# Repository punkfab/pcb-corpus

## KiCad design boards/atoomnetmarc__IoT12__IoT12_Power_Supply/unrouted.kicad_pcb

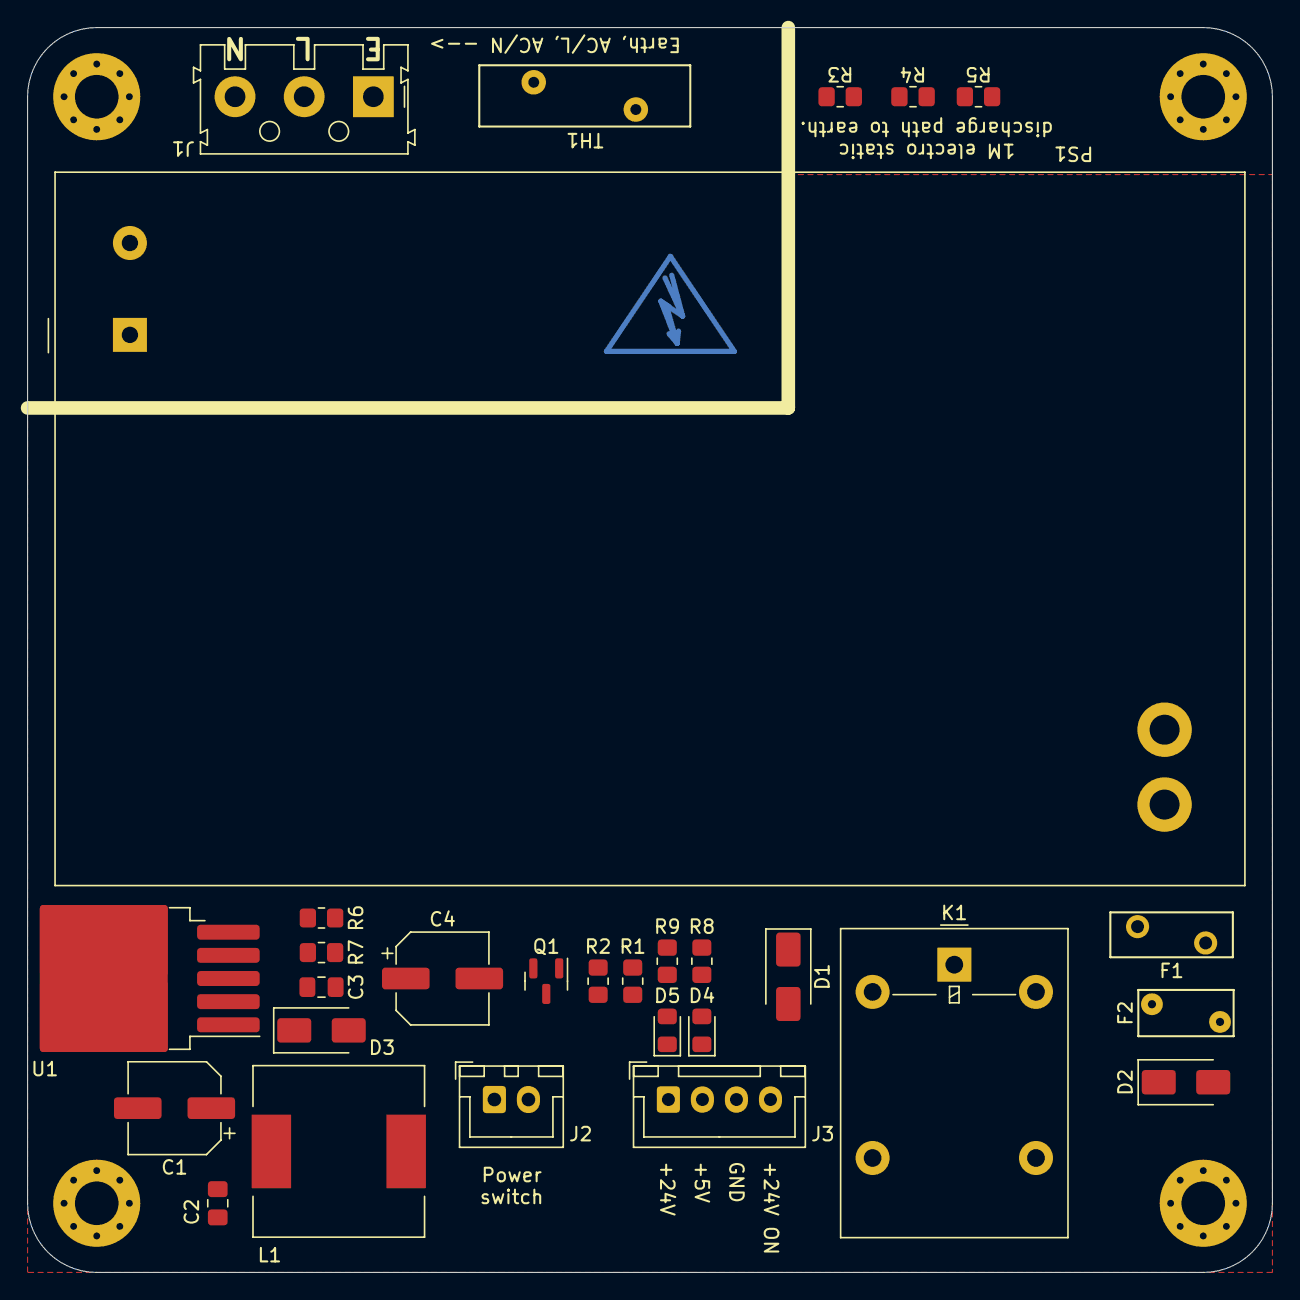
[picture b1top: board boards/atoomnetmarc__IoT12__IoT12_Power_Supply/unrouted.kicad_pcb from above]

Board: 2 copper layers, 91.4 x 91.4 mm, 33 parts (0 on the bottom side), 21 nets, no tracks yet.

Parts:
C1, C4: 100uF/35V; CP_Elec_6.3x7.7
C2, C3: 100nF; C_0805_2012Metric_Pad1.18x1.45mm_HandSolder
D1: SS14; D_SMA
D2, D3: SS34; D_SMA
D4, D5: Blue; LED_0805_2012Metric_Pad1.15x1.40mm_HandSolder
F1: PTC 1.5A/30V; RV_Disc_D9mm_W3.3mm_P5mm
F2: PTC 0.5A/30V; RV_Disc_D7mm_W3.4mm_P5mm
H1, H2, H3, H4: MountingHole; MountingHole_3.2mm_M3_Pad_Via
J1: Screw_Terminal_01x03; TerminalBlock_Weidmueller-PM-5.08-03-90-3.5SN-BK-BX
J2: JST B2B-XH-A; JST_XH_B2B-XH-A_1x02_P2.50mm_Vertical
J3: JST B4B-XH-A; JST_XH_B4B-XH-A_1x04_P2.50mm_Vertical
K1: Omron G5LE-1 24VDC; Relay_SPDT_Omron-G5LE-1
L1: 68uH; L_12x12mm_H8mm
PS1: MPM-90-24; Converter_ACDC_MeanWell_MPM-90-xx_THT
Q1: MMBT2222; SOT-23
R1, R3, R4, R5: 330k; R_0805_2012Metric_Pad1.20x1.40mm_HandSolder
R2, R6: 1k; R_0805_2012Metric_Pad1.20x1.40mm_HandSolder
R7: 3k3; R_0805_2012Metric_Pad1.20x1.40mm_HandSolder
R8: 2k2; R_0805_2012Metric_Pad1.20x1.40mm_HandSolder
R9: 22k; R_0805_2012Metric_Pad1.20x1.40mm_HandSolder
TH1: 10D-15; RV_Disc_D15.5mm_W4.5mm_P7.5mm
U1: LM2596S-ADJ; TO-263-5_TabPin3

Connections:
24V_ON: J3.4, R1.1, R2.2
24V_SWITCHED: J3.1, K1.3, R9.1
+5V: C3.1, C4.1, J3.2, L1.2, R7.1, R8.1
+24V: F1.2, F2.2, PS1.3 (+Vout)
/L: J1.2, TH1.1
/N: J1.3, PS1.2 (AC/N)
/SW_A: D1.2 (A), J2.1, K1.5
/SW_B: J2.2, Q1.3 (C)
Earth: J1.1, R3.1
GND: C1.2, C2.2, C3.2, C4.2, D3.2 (A), D4.1 (K), D5.1 (K), J3.3, PS1.4 (-Vout), Q1.2 (E), R1.2, R5.2, R6.1, U1.3 (GND), U1.5 (~ON/OFF)
unnamed: D1.1 (K), F1.1, K1.1, K1.2
unnamed: D2.2 (A), F2.1
unnamed: C1.1, C2.1, D2.1 (K), U1.1 (VIN)
unnamed: D3.1 (K), L1.1, U1.2 (OUT)
unnamed: D4.2 (A), R8.2
unnamed: D5.2 (A), R9.2
unnamed: PS1.1 (AC/L), TH1.2
unnamed: Q1.1 (B), R2.1
unnamed: R3.2, R4.1
unnamed: R4.2, R5.1
unnamed: R6.2, R7.2, U1.4 (FB)

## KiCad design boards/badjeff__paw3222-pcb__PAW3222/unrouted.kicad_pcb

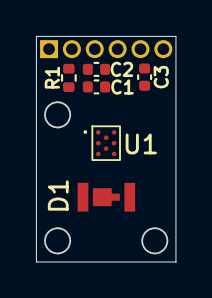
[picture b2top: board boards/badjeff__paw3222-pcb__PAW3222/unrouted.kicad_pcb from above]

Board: 2 copper layers, 7.8 x 12.5 mm, 7 parts (0 on the bottom side), 9 nets, no tracks yet.

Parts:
C1: 0.1uF; C_0402_1005Metric
C2: 10uF; C_0402_1005Metric
C3: 4.7uF; C_0402_1005Metric
D1: IR LED LTE-C216-P-W; LTE-C216-P-W
J1: Conn_01x06_Socket; PinHeader_1x06_P1.27mm_Vertical
R1: 51R; R_0402_1005Metric
U1: PAW3220LU; PAW3222LU

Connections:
GND: C1.2, C2.2, C3.2, J1.2, U1.C1 (VSS)
MOTION: J1.4, U1.B2 (MOTION)
NCS: J1.5, U1.A3 (NCS)
unnamed: D1.2 (A), R1.1
unnamed: D1.1 (K), U1.E1 (LED)
unnamed: C3.1, U1.A1 (VDDA)
SCLK: J1.3, U1.D2 (SCLK)
SDIO: J1.6, U1.C3 (SDIO)
VCC 3.3V: C1.1, C2.1, J1.1, R1.2, U1.E3 (VDD)

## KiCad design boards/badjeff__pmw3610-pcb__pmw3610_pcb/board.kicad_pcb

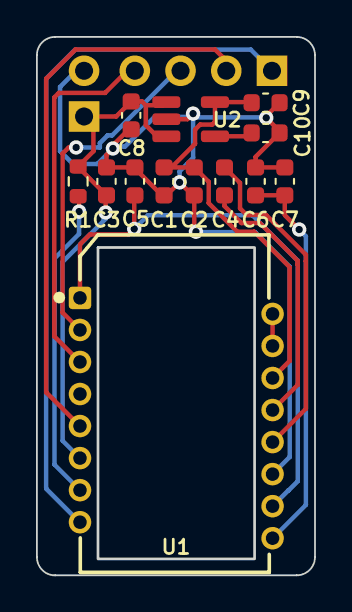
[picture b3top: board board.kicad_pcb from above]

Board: 2 copper layers, 15.4 x 29.9 mm, 15 parts (0 on the bottom side), 14 nets.

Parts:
C1: 3.3uF/16V; C_0603_1608Metric
C2, C3: 100nF; C_0603_1608Metric
C4: 100nF X7R; C_0603_1608Metric
C5: 10nF; C_0603_1608Metric
C6: 10uF X7R; C_0603_1608Metric
C7: 10nF X7R; C_0603_1608Metric
C8, C9: 1uF; C_0603_1608Metric
C10: 22nF; C_0603_1608Metric
J1: Conn_01x02; PinHeader_1x02_P2.54mm_Vertical
J2: Conn_01x04; PinHeader_1x04_P2.54mm_Vertical
R1: 10k; R_0603_1608Metric
U1: PMW3610; PMW3610DM-SUDU 16Pin
U2: TLV74318PDBVR; SOT-23-5_HandSoldering

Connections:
+1V8: C1.1, C2.1, C9.1, U1.14 (VDD), U2.5 (OUT)
GND: C1.2, C2.2, C3.2, C5.2, C6.2, C7.2, C8.2, C9.2, C10.2, J1.2, U1.11 (GND), U2.2 (GND)
MOTION: J2.1, U1.8 (MOTION)
unnamed: C5.1, U1.1 (+VCSEL), U1.10 (PASS_T)
unnamed: U1.15 (XYLASER), U1.16 (-VCSEL)
unnamed: C4.2, U1.13 (CN)
unnamed: C4.1, U1.12 (CP)
unnamed: R1.2, U1.7 (NRESET)
unnamed: C6.1, C7.1, U1.9 (VCP)
unnamed: C10.1, U2.4 (NC)
SCLK: J2.4, U1.3 (SCLK)
SDIO: J2.3, U1.2 (SDIO)
VIN: C3.1, C8.1, J1.1, R1.1, U1.6 (VDDIO), U2.1 (IN), U2.3 (EN)
nCS: J2.2, U1.5 (NCS)

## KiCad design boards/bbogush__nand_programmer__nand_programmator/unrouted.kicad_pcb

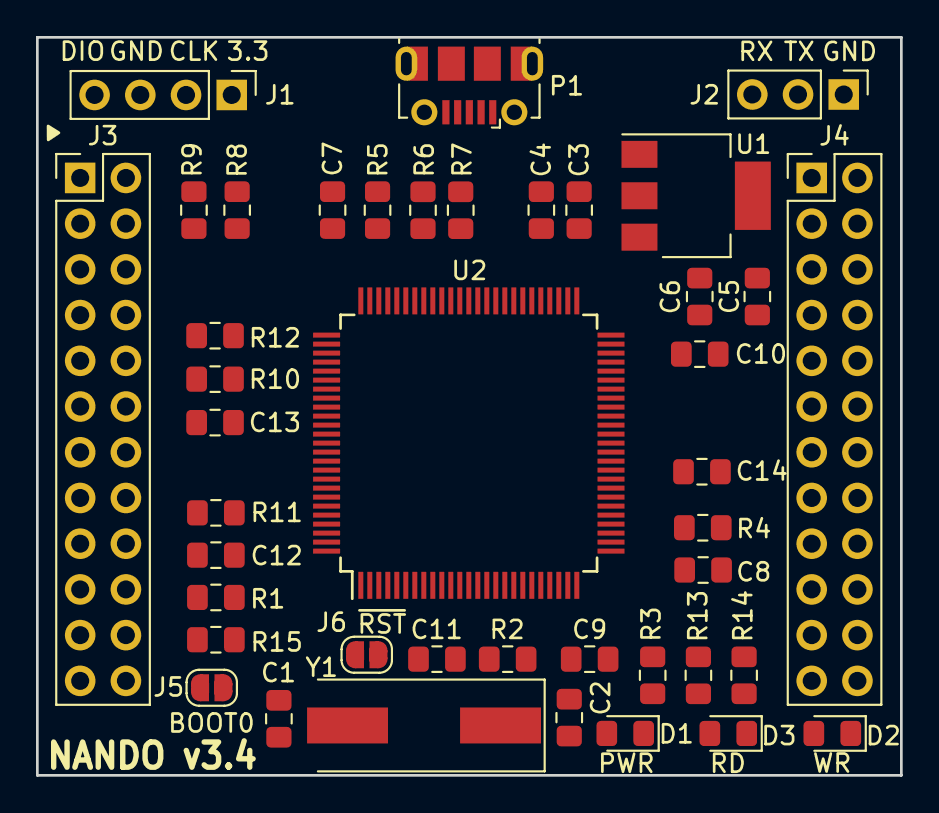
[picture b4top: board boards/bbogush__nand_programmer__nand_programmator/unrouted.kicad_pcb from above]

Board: 2 copper layers, 48.0 x 41.0 mm, 42 parts (0 on the bottom side), 49 nets, no tracks yet.

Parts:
C1, C2: 30pF; C_0805_2012Metric_Pad1.15x1.40mm_HandSolder
C3, C6: 10uF; C_0805_2012Metric_Pad1.15x1.40mm_HandSolder
C4, C5, C7, C8, C9, C10, C11, C12, C13, C14: 0.1uF; C_0805_2012Metric_Pad1.15x1.40mm_HandSolder
D1: GREEN; LED_0805_2012Metric_Pad1.15x1.40mm_HandSolder
D2: RED; LED_0805_2012Metric_Pad1.15x1.40mm_HandSolder
D3: YELLOW; LED_0805_2012Metric_Pad1.15x1.40mm_HandSolder
J1: Conn_01x04; PinHeader_1x04_P2.54mm_Vertical
J2: Conn_01x03; PinHeader_1x03_P2.54mm_Vertical
J3: Conn_02x12_Odd_Even_Left; PinHeader_2x12_P2.54mm_Vertical
J4: Conn_02x12_Odd_Even_Right; PinHeader_2x12_P2.54mm_Vertical_2
J5: BOOT0; SolderJumper-2_P1.3mm_Open_RoundedPad1.0x1.5mm
J6: ~{RST}; SolderJumper-2_P1.3mm_Open_RoundedPad1.0x1.5mm
P1: USB; USB_Micro-B_Molex-105017-0001
R1: 510; R_0805_2012Metric_Pad1.15x1.40mm_HandSolder
R2, R4, R8, R9, R10, R11, R12, R15: 10k; R_0805_2012Metric_Pad1.15x1.40mm_HandSolder
R3, R13, R14: 1k; R_0805_2012Metric_Pad1.15x1.40mm_HandSolder
R5: 1.5k; R_0805_2012Metric_Pad1.15x1.40mm_HandSolder
R6, R7: 22; R_0805_2012Metric_Pad1.15x1.40mm_HandSolder
U1: LM1117-3.3; SOT-223
U2: STM32F103VCT6; LQFP-100_14x14mm_Pitch0.5mm
Y1: Crystal_SMD_8MHz_18pF; Crystal_SMD_HC49-SD

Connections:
+3V3: C5.1, C6.1, C7.1, C8.1, C9.1, C10.1, C11.1, C12.1, C13.2, C14.2, J1.1, J3.12, J4.34, J4.37, J4.39, R1.1, R2.1, R3.2, R5.2, R9.1, R10.2, R11.2, R12.1, U1.2, U1.4, U2.6, U2.11, U2.22, U2.28, U2.50, U2.75, U2.100
+5V: C3.1, C4.1, P1.1, U1.3
/BOOT0: J5.1, R15.2, U2.94
/FSMC_ALE: J3.17, U2.59
/FSMC_CLE: J3.16, U2.58
/FSMC_D0: J4.29, U2.61
/FSMC_D1: J4.30, U2.62
/FSMC_D2: J4.31, U2.81
/FSMC_D3: J4.32, U2.82
/FSMC_D4: J4.41, U2.38
/FSMC_D5: J4.42, U2.39
/FSMC_D6: J4.43, U2.40
/FSMC_D7: J4.44, U2.41
/FSMC_D8: J4.26, U2.42
/FSMC_D9: J4.27, U2.43
/FSMC_D10: J4.28, U2.44
/FSMC_D11: J4.33, U2.45
/FSMC_D12: J4.40, U2.46
/FSMC_D13: J4.45, U2.55
/FSMC_D14: J4.46, U2.56
/FSMC_D15: J4.47, U2.57
/FSMC_NCE2: J3.9, R10.1, U2.88
/FSMC_NOE: J3.8, U2.85
/FSMC_NWAIT: J3.7, R12.2, U2.87
/FSMC_NWE: J3.18, U2.86
/NRST: J6.2, R2.2, U2.14
/RED: R13.2, U2.23
/SPI1_MISO: J3.3, U2.31
/SPI1_MOSI: J3.4, U2.32
/SPI1_NSS: J3.1, U2.29
/SPI1_SCK: J3.2, U2.30
/SWCLK: J1.2, R8.2, U2.76
/SWDIO: J1.4, R9.2, U2.72
/USART1_RX: J2.3, U2.69
/USART1_TX: J2.2, U2.68
/USB_DN: R7.1, U2.70
/USB_DP: R6.1, U2.71
/USB_N: P1.2, R7.2
/USB_P: P1.3, R5.1, R6.2
/YELLOW: R14.2, U2.24
GNDD: C1.2, C2.2, C3.2, C4.2, C5.2, C6.2, C7.2, C8.2, C9.2, C10.2, C11.2, C12.2, C13.1, C14.1, D1.1, D2.1, D3.1, J1.3, J2.1, J3.13, J4.25, J4.36, J4.48, J6.1, P1.5, P1.6, R4.1, R8.1, R15.1, U1.1, U2.10, U2.19, U2.27, U2.49, U2.74, U2.99
unnamed: C1.1, U2.12, Y1.2
unnamed: C2.1, U2.13, Y1.1
unnamed: D1.2, R3.1
unnamed: D2.2, R13.1
unnamed: D3.2, R14.1
unnamed: J3.19, R11.1
unnamed: J5.2, R1.2
unnamed: R4.2, U2.37

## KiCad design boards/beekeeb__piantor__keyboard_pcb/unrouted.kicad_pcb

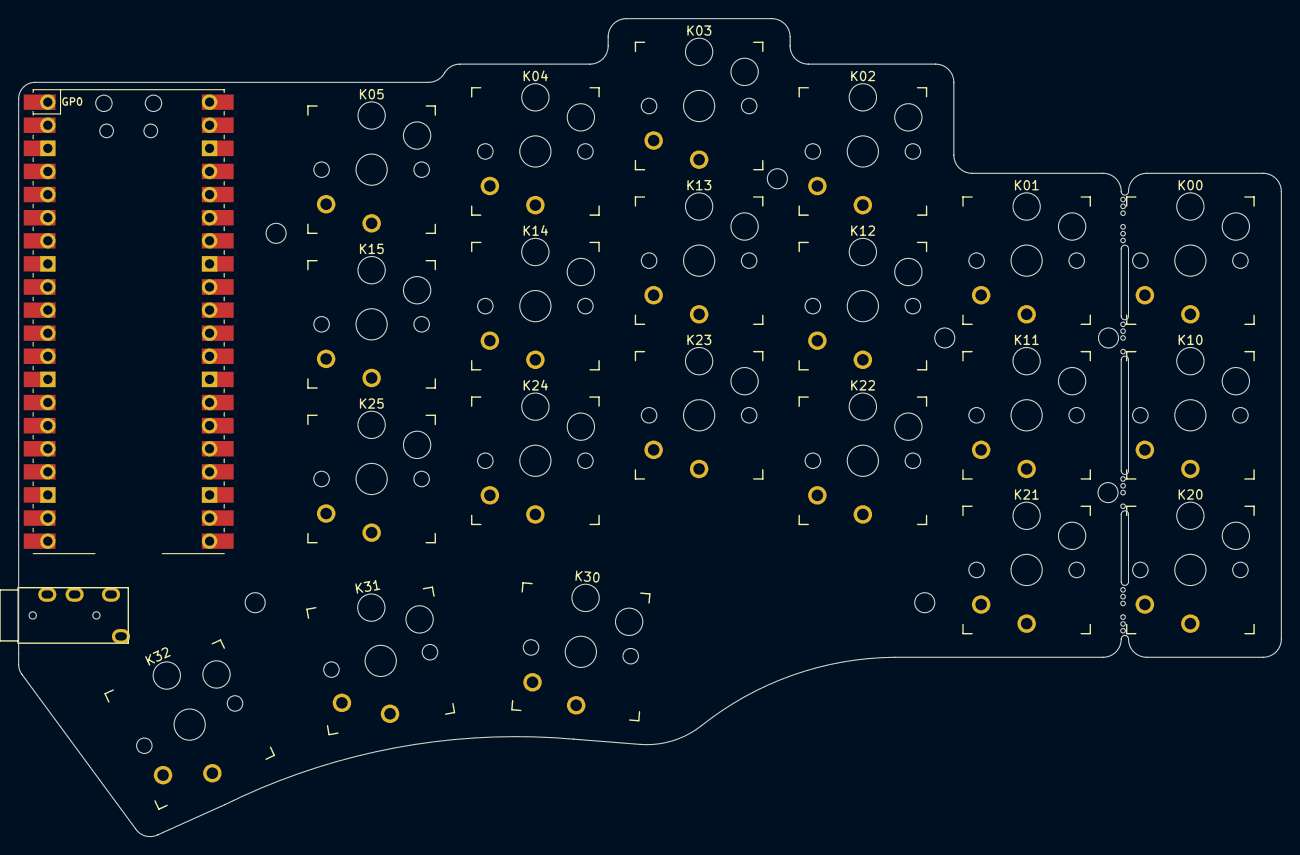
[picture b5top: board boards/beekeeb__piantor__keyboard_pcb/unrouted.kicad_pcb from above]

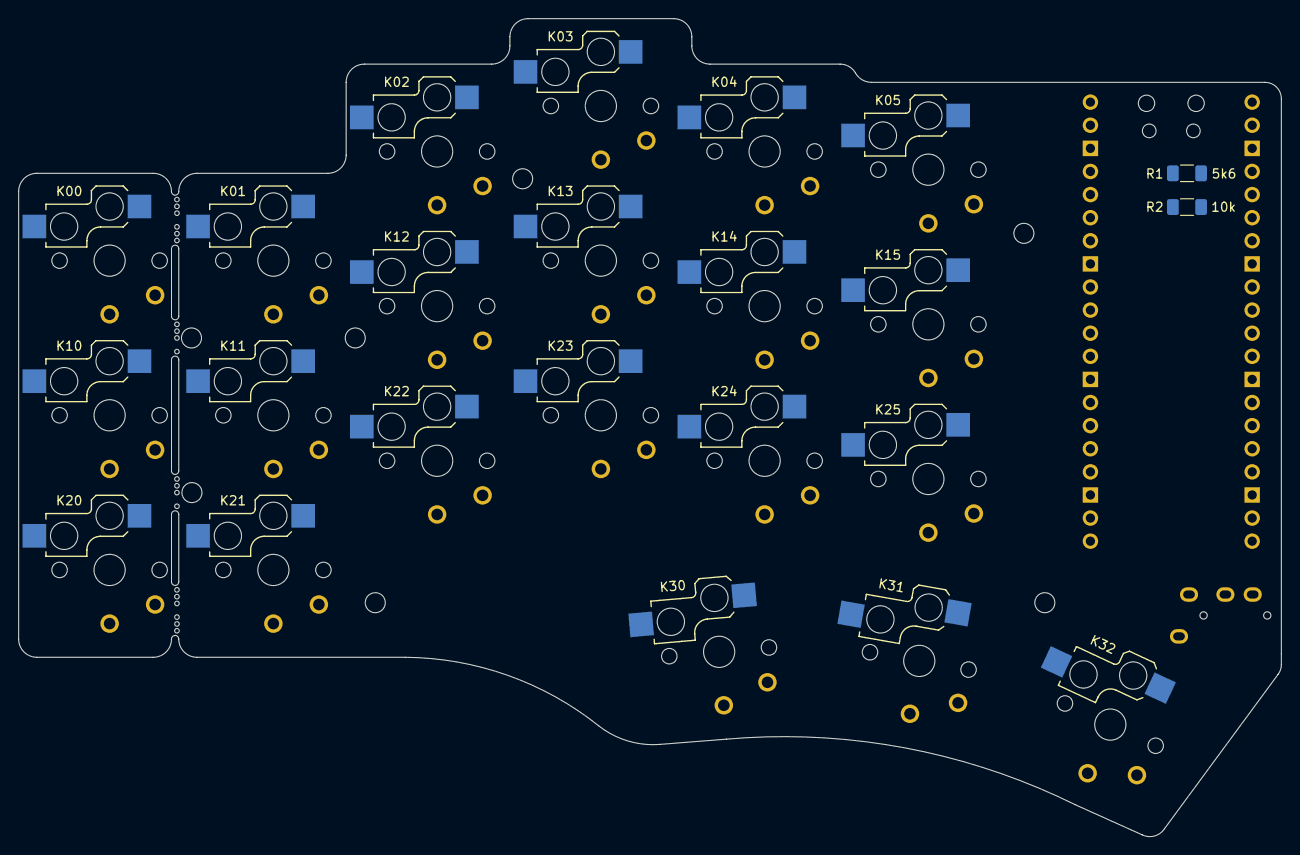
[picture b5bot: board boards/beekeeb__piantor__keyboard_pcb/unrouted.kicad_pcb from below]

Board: 2 copper layers, 138.8 x 89.9 mm, 36 parts (13 on the bottom side), 27 nets, no tracks yet.

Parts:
H1, H1#2, H2, H3, H4, H4#2, H4#3: MountingHole; MountingHole_2.2mm_M2-8mm
J1: TRRS; TRRS-PJ-320A
K00, K01, K02, K03, K04, K05, K10, K11, K12, K13, K14, K15, K20, K21, K22, K23, K24, K25, K30, K31, K32: KEYSW; Kailh_socket_PG1350_optional
MB1, MB2: MountingHole; mousebites_2
MB3, MB4: MountingHole; mousebites_3
R1: 5k6; R_1206_3216Metric_Pad1.30x1.75mm_HandSolder
R2: 10k; R_1206_3216Metric_Pad1.30x1.75mm_HandSolder
U2: Pico; RPi_Pico_SMD_TH

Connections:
/k00: K00.1, U2.15 (GPIO11)
/k01: K01.1, U2.11 (GPIO8)
/k02: K02.1, U2.7 (GPIO5)
/k03: K03.1, U2.4 (GPIO2)
/k04: K04.1, U2.27 (GPIO21)
/k05: K05.1, U2.29 (GPIO22)
/k10: K10.1, U2.16 (GPIO12)
/k11: K11.1, U2.12 (GPIO9)
/k12: K12.1, U2.9 (GPIO6)
/k13: K13.1, U2.5 (GPIO3)
/k14: K14.1, U2.25 (GPIO19)
/k15: K15.1, U2.26 (GPIO20)
/k20: K20.1, U2.17 (GPIO13)
/k21: K21.1, U2.14 (GPIO10)
/k22: K22.1, U2.10 (GPIO7)
/k23: K23.1, U2.6 (GPIO4)
/k24: K24.1, U2.22 (GPIO17)
/k25: K25.1, U2.24 (GPIO18)
/k30: K30.1, U2.21 (GPIO16)
/k31: K31.1, U2.19 (GPIO14)
/k32: K32.1, U2.20 (GPIO15)
GND: J1.3 (RING1), K00.2, K01.2, K02.2, K03.2, K04.2, K05.2, K10.2, K11.2, K12.2, K13.2, K14.2, K15.2, K20.2, K21.2, K22.2, K23.2, K24.2, K25.2, K30.2, K31.2, K32.2, R2.2, U2.3 (GND), U2.8 (GND), U2.13 (GND), U2.18 (GND), U2.23 (GND), U2.28 (GND), U2.33 (AGND), U2.38 (GND)
VBUS: R1.1, U2.40 (VBUS)
VCC: J1.2 (TIP), U2.39 (VSYS)
rx: J1.4 (RING2), U2.2 (GPIO1)
tx: J1.1 (SLEEVE), U2.1 (GPIO0)
vbus_sense: R1.2, R2.1, U2.34 (GPIO28_ADC2)

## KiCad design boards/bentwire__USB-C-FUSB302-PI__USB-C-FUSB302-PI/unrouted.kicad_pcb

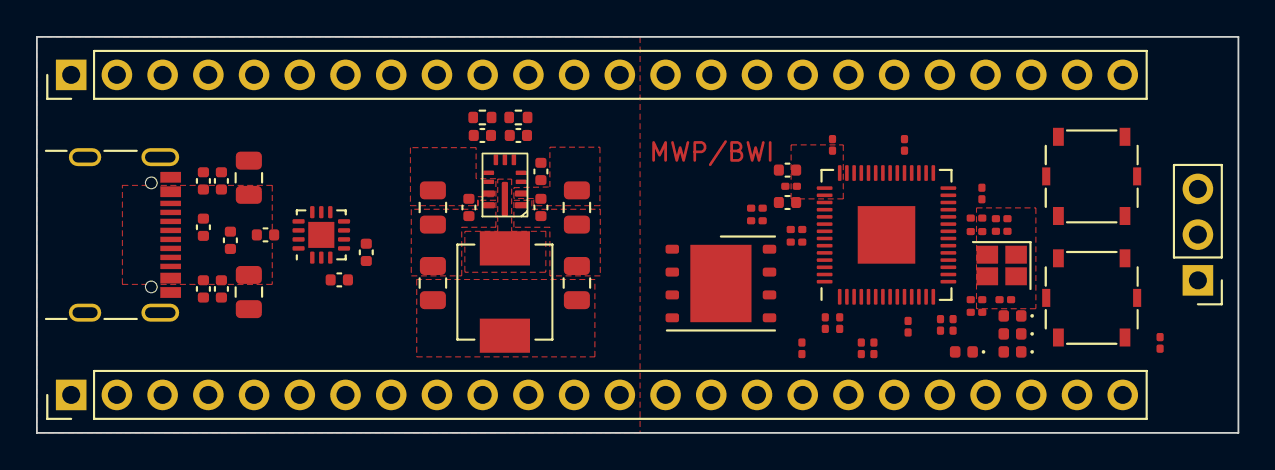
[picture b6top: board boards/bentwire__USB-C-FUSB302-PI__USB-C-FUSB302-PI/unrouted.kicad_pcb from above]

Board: 4 copper layers, 66.8 x 22.0 mm, 64 parts (0 on the bottom side), 58 nets, no tracks yet.

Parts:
C1, C9, C16, C17: 4.7uF 50V X5R; C_0805_2012Metric
C2, C3, C12, C13, C14, C15, C18, C19: 0.1uF 50V X5R; C_0402_1005Metric
C4, C20: 1uF 10V X7S; C_0402_1005Metric
C5: 0.1uF 10V X7R; C_0402_1005Metric
C6: 11pF 50V; C_0402_1005Metric
C7, C8: 22uF 10V X5R; C_0805_2012Metric
C10, C11: 330pF 50V; C_0402_1005Metric
C301, C302: 1uF 6.3V; C_0402_1005Metric
C303, C304, C305, C306, C307, C308, C309, C310, C311: 100nF 6.3V; C_0201_0603Metric
C312, C313: 27pF; C_0201_0603Metric
D301, D302, D303, D304: TZ-P2-0402GTIA1-0.45T; LED_0402_1005Metric
J1: USB_C_Receptacle_USB2.0; USB_C_Receptacle_GCT_USB4105-xx-A_16P_TopMnt_Horizontal
J101, J102: Conn_01x24; PinHeader_1x24_P2.54mm_Vertical
J301: Conn_01x03; PinHeader_1x03_P2.54mm_Vertical
L1: 6.8uH IHLP2020BZER6R8M01; L_Vishay_IHLP-2020
R1: 100K; R_0402_1005Metric
R2: 43.2K; R_0402_1005Metric
R301, R304, R309: 10K; R_0201_0603Metric
R302, R303: 27R4; R_0201_0603Metric
R305, R306: 1K; R_0201_0603Metric
R307, R308: 4.7K; R_0201_0603Metric
R310, R311, R312, R313: 470R; R_0201_0603Metric
SW301: RUN; SW_SPST_Panasonic_EVQPL_3PL_5PL_PT_A15
SW302: BOOT; SW_SPST_Panasonic_EVQPL_3PL_5PL_PT_A15
U1: FUSB302BMPX; WQFN-14-1EP_2.5x2.5mm_P0.5mm_EP1.45x1.45mm
U2: LMR36006CRNX; TI-RNX0012A-VQFN-HR
U301: W25Q128JVPIQ; WSON-8-1EP_6x5mm_P1.27mm_EP3.4x4.3mm
U302: RP2040; QFN-56-1EP_7x7mm_P0.4mm_EP3.2x3.2mm
Y301: 12.000 MHz; Crystal_SMD_EuroQuartz_X22-4Pin_2.5x2.0mm

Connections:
+3V3: C6.2, C7.2, C8.2, C18.1, C19.1, C20.1, C301.2, C303.2, C304.2, C305.2, C306.2, C307.2, C308.2, C311.1, J101.10, J101.11, J102.10, J102.11, L1.2, R1.1, R301.1, R304.1, R307.1, R308.1, R309.1, U1.3 (VDD), U1.4 (VDD), U1.12 (VCONN), U1.13 (VCONN), U301.8 (VCC), U302.1 (IOVDD), U302.10 (IOVDD), U302.22 (IOVDD), U302.33 (IOVDD), U302.42 (IOVDD), U302.43 (ADC_AVDD), U302.44 (VREG_IN), U302.48 (USB_VDD), U302.49 (IOVDD)
/RP2040 CPU/ADC0: J102.17, U302.38 (GPIO26_ADC0)
/RP2040 CPU/ADC1: J102.16, U302.39 (GPIO27_ADC1)
/RP2040 CPU/ADC2: J102.15, U302.40 (GPIO28_ADC2)
/RP2040 CPU/ADC3: J102.14, U302.41 (GPIO29_ADC3)
/RP2040 CPU/D+: J1.A6 (D+), J1.B6 (D+), R302.1
/RP2040 CPU/D-: J1.A7 (D-), J1.B7 (D-), R303.1
/RP2040 CPU/GPIO2: J101.16, R309.2, U1.5 (INT_N), U302.4 (GPIO2)
/RP2040 CPU/GPIO3: J101.17, U302.5 (GPIO3)
/RP2040 CPU/GPIO4: J101.18, U302.6 (GPIO4)
/RP2040 CPU/GPIO5: J101.19, U302.7 (GPIO5)
/RP2040 CPU/GPIO8: J101.22, U302.11 (GPIO8)
/RP2040 CPU/GPIO9: J101.23, U302.12 (GPIO9)
/RP2040 CPU/GPIO10: J101.24, U302.13 (GPIO10)
/RP2040 CPU/GPIO20: J102.24, U302.31 (GPIO20)
/RP2040 CPU/GPIO21: J102.23, U302.32 (GPIO21)
/RP2040 CPU/GPIO22: J102.22, U302.34 (GPIO22)
/RP2040 CPU/GPIO23: J102.21, U302.35 (GPIO23)
/RP2040 CPU/GPIO24: J102.20, U302.36 (GPIO24)
/RP2040 CPU/GPIO25: J102.19, U302.37 (GPIO25)
/RP2040 CPU/I2C0_SCL: J101.15, R308.2, U1.6 (SCL), U302.3 (GPIO1)
/RP2040 CPU/I2C0_SDA: J101.14, R307.2, U1.7 (SDA), U302.2 (GPIO0)
/RP2040 CPU/I2C1_SCL: J101.21, U302.9 (GPIO7)
/RP2040 CPU/I2C1_SDA: J101.20, U302.8 (GPIO6)
/RP2040 CPU/RUN: R301.2, SW301.2, U302.26 (RUN)
/USB-C + PP/SBU1: J1.A8 (SBU1), J101.3
/USB-C + PP/SBU2: J1.B8 (SBU2), J101.2
/USB-C + PP/VBUS: C1.1, C2.1, C3.1, C9.1, C12.1, C13.1, C14.1, C15.1, C16.1, C17.1, J1.A4 (VBUS), J1.A9 (VBUS), J1.B4 (VBUS), J1.B9 (VBUS), J101.5, J101.6, J102.4, J102.5, J102.6, U1.2 (VBUS), U2.2 (VIN), U2.9 (EN), U2.10 (VIN)
GND: C1.2, C2.2, C3.2, C4.2, C7.1, C8.1, C9.2, C10.1, C11.1, C12.2, C13.2, C14.2, C15.2, C16.2, C17.2, C18.2, C19.2, C20.2, C301.1, C302.1, C303.1, C304.1, C305.1, C306.1, C307.1, C308.1, C309.1, C310.1, C311.2, C312.2, C313.2, D301.1 (K), D302.1 (K), D303.1 (K), D304.1 (K), J1.A1 (GND), J1.A12 (GND), J1.B1 (GND), J1.B12 (GND), J1.S1 (SHIELD), J101.1, J101.4, J101.7, J101.8, J101.9, J101.12, J101.13, J102.1, J102.2, J102.3, J102.7, J102.8, J102.9, J102.12, J102.13, J102.18, J301.2, R2.2, SW301.1, SW302.1, U1.8 (GND), U1.9 (GND), U1.15 (GND), U2.1 (PGND), U2.6 (AGND), U2.11 (PGND), U301.4 (GND), U302.57 (GND), Y301.2, Y301.4
unnamed: C312.1, R306.1, Y301.1
unnamed: D301.2 (A), R310.2
unnamed: D302.2 (A), R311.2
unnamed: D303.2 (A), R312.2
unnamed: D304.2 (A), R313.2
unnamed: C11.2, J1.A5 (CC1), U1.10 (CC1), U1.11 (CC1)
unnamed: C10.2, J1.B5 (CC2), U1.1 (CC2), U1.14 (CC2)
unnamed: J301.1, U302.24 (SWCLK)
unnamed: J301.3, U302.25 (SWD)
unnamed: R305.1, SW302.2
unnamed: C5.1, U2.4 (BOOT)
unnamed: C6.1, R1.2, R2.1, U2.7 (FB)
unnamed: C5.2, L1.1, U2.3 (NC/SW), U2.12 (SW)
unnamed: C4.1, U2.5 (VCC)
unnamed: U301.6 (CLK), U302.52 (QSPI_SCLK)
unnamed: U301.5 (DI(IO0)), U302.53 (QSPI_SD0)
unnamed: U301.2 (DO(IO1)), U302.55 (QSPI_SD1)
unnamed: U301.3 (IO2), U302.54 (QSPI_SD2)
unnamed: U301.7 (IO3), U302.51 (QSPI_SD3)
unnamed: R304.2, R305.2, U301.1 (~CS), U302.56 (QSPI_SS)
unnamed: R310.1, U302.14 (GPIO11)
unnamed: R311.1, U302.15 (GPIO12)
unnamed: R312.1, U302.16 (GPIO13)
unnamed: R313.1, U302.17 (GPIO14)
unnamed: R303.2, U302.46 (USB_DM)
unnamed: R302.2, U302.47 (USB_DP)
unnamed: C302.2, C309.2, C310.2, U302.23 (DVDD), U302.45 (VREG_VOUT), U302.50 (DVDD)
unnamed: C313.1, U302.20 (XIN), Y301.3
unnamed: R306.2, U302.21 (XOUT)

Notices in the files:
boards/atoomnetmarc__IoT12__IoT12_Power_Supply/unrouted.kicad_pcb:
Apache License, Version 2.0
boards/badjeff__pmw3610-pcb__pmw3610_pcb/board.kicad_pcb:
Open Source Hardware, CERN-OHL-P v2
